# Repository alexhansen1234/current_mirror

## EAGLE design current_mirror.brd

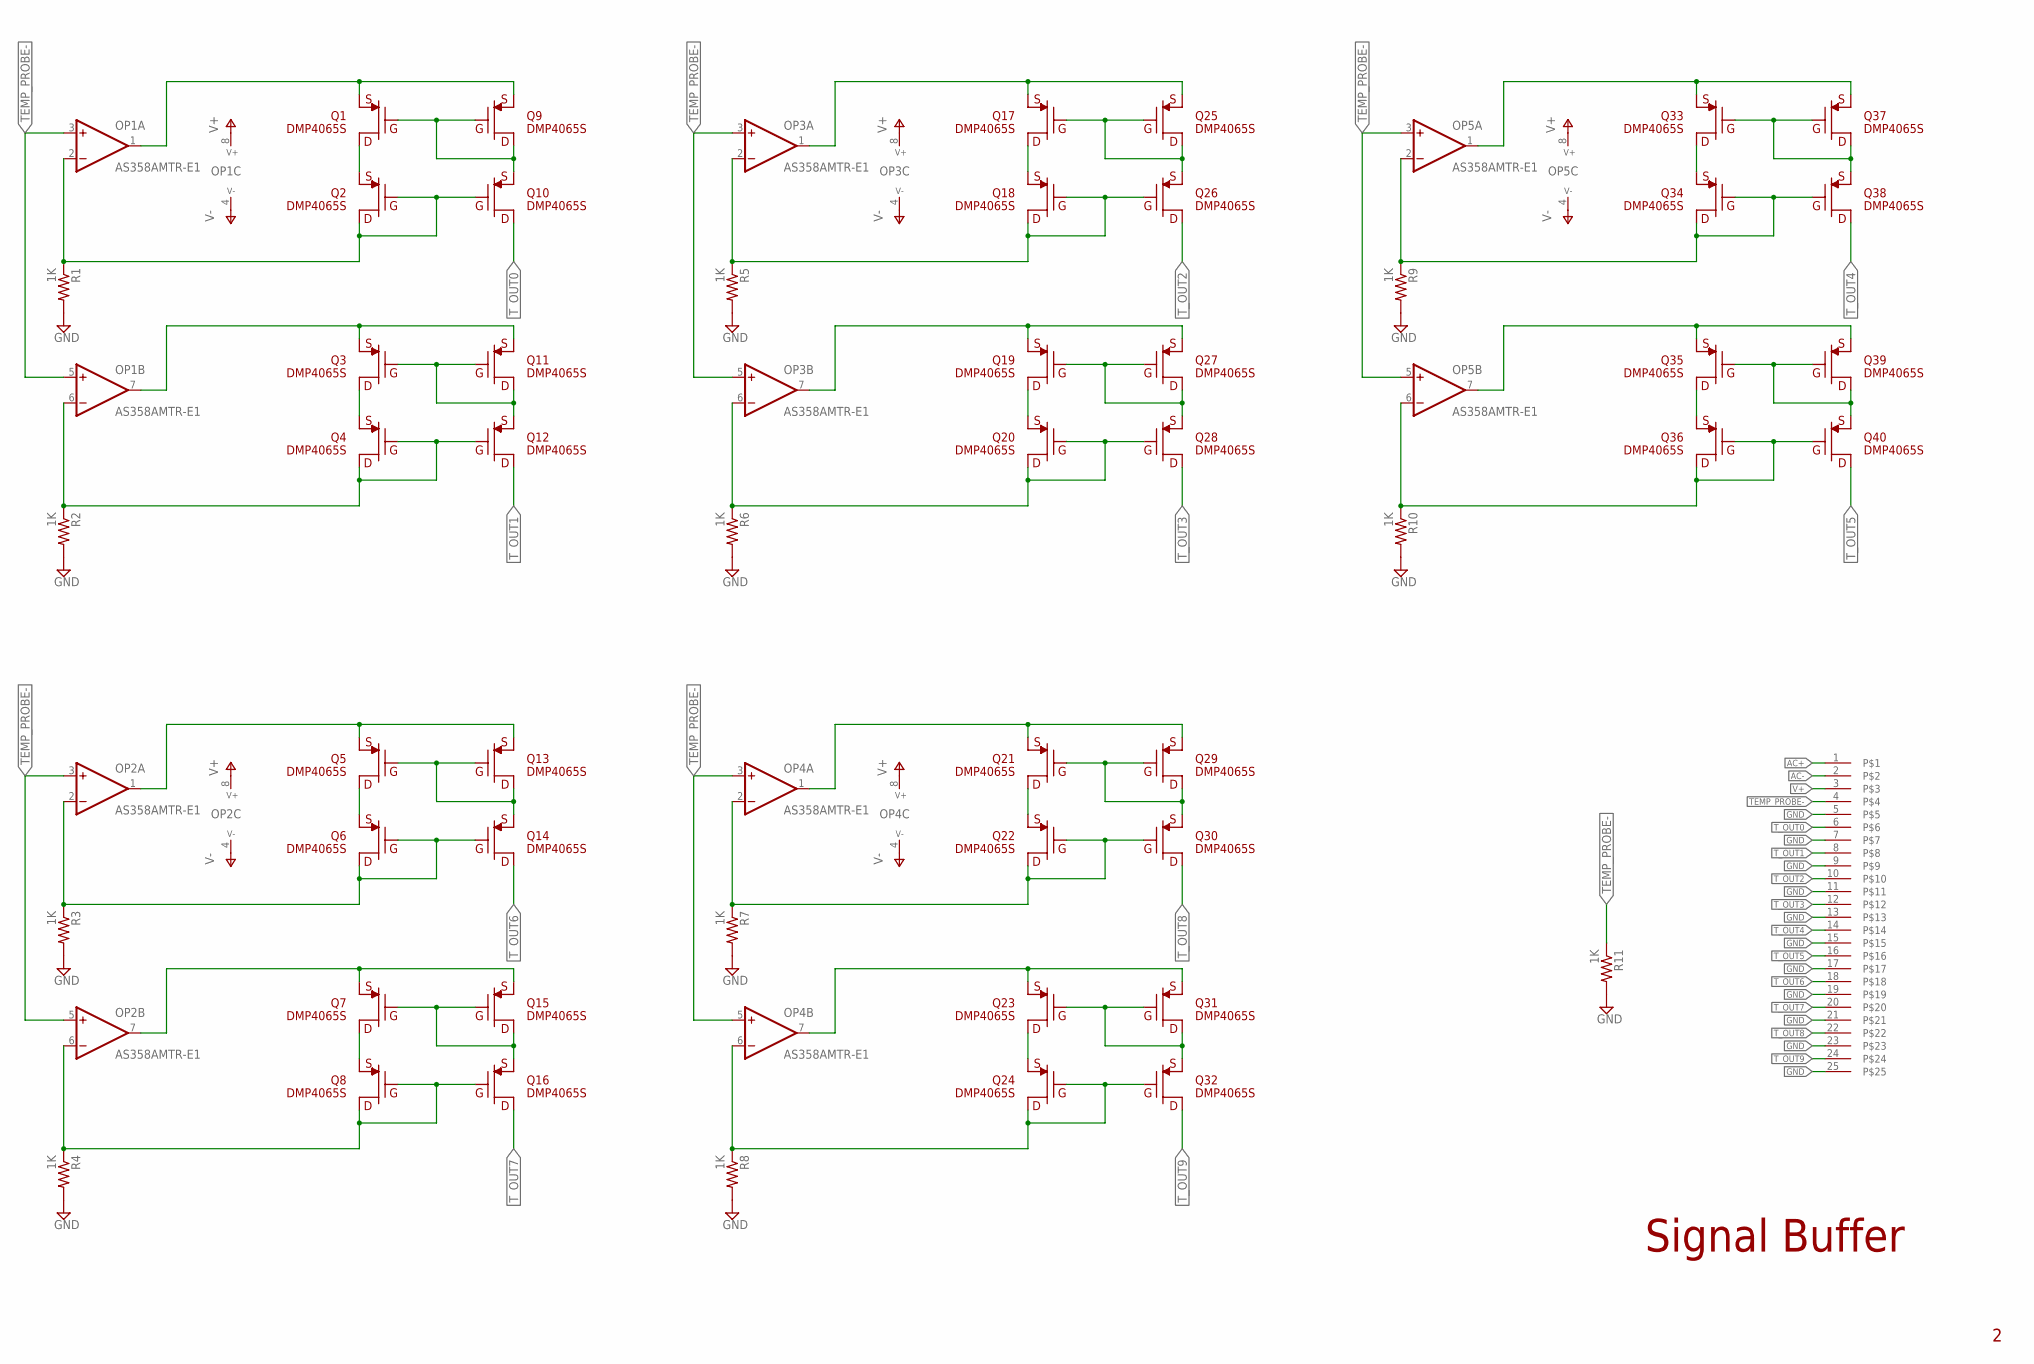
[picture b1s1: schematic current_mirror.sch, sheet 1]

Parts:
J1: 2-282836-6; SCREW_TERMINAL_25
OP1, OP2, OP3, OP4, OP5: AS358AMTR-E1; SOIC-8
Q1, Q2, Q3, Q4, Q5, Q6, Q7, Q8, Q9, Q10, Q11, Q12, Q13, Q14, Q15, Q16, Q17, Q18, Q19, Q20, Q21, Q22, Q23, Q24, Q25, Q26, Q27, Q28, Q29, Q30, Q31, Q32, Q33, Q34, Q35, Q36, Q37, Q38, Q39, Q40: DMP4065S; SOT23
R1, R2, R3, R4, R5, R6, R7, R8, R9, R10, R11: 1K; R1206

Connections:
AC+: J1.1; also elsewhere on the board
AC-: J1.2; also elsewhere on the board
GND: J1.5, J1.7, J1.9, J1.11, J1.13, J1.15, J1.17, J1.19, J1.21, J1.23, J1.25, R1.2, R2.2, R3.2, R4.2, R5.2, R6.2, R7.2, R8.2, R9.2, R10.2, R11.2; also elsewhere on the board
unnamed: OP1.1 (OUT), Q1.2 (S1), Q9.2 (S1)
unnamed: Q1.1 (G1), Q9.1 (G1), Q9.3 (D1), Q10.2 (S1)
unnamed: Q1.3 (D1), Q2.2 (S1)
unnamed: OP1.7 (OUT), Q3.2 (S1), Q11.2 (S1)
unnamed: OP1.2 (-IN), Q2.1 (G1), Q2.3 (D1), Q10.1 (G1), R1.1
unnamed: Q3.1 (G1), Q11.1 (G1), Q11.3 (D1), Q12.2 (S1)
unnamed: Q3.3 (D1), Q4.2 (S1)
unnamed: OP1.6 (-IN), Q4.1 (G1), Q4.3 (D1), Q12.1 (G1), R2.1
unnamed: OP3.1 (OUT), Q17.2 (S1), Q25.2 (S1)
unnamed: Q17.1 (G1), Q25.1 (G1), Q25.3 (D1), Q26.2 (S1)
unnamed: Q17.3 (D1), Q18.2 (S1)
unnamed: OP3.2 (-IN), Q18.1 (G1), Q18.3 (D1), Q26.1 (G1), R5.1
unnamed: OP3.7 (OUT), Q19.2 (S1), Q27.2 (S1)
unnamed: Q19.1 (G1), Q27.1 (G1), Q27.3 (D1), Q28.2 (S1)
unnamed: Q19.3 (D1), Q20.2 (S1)
unnamed: OP3.6 (-IN), Q20.1 (G1), Q20.3 (D1), Q28.1 (G1), R6.1
unnamed: OP5.1 (OUT), Q33.2 (S1), Q37.2 (S1)
unnamed: Q33.1 (G1), Q37.1 (G1), Q37.3 (D1), Q38.2 (S1)
unnamed: Q33.3 (D1), Q34.2 (S1)
unnamed: OP5.2 (-IN), Q34.1 (G1), Q34.3 (D1), Q38.1 (G1), R9.1
unnamed: OP5.7 (OUT), Q35.2 (S1), Q39.2 (S1)
unnamed: Q35.1 (G1), Q39.1 (G1), Q39.3 (D1), Q40.2 (S1)
unnamed: Q35.3 (D1), Q36.2 (S1)
unnamed: OP5.6 (-IN), Q36.1 (G1), Q36.3 (D1), Q40.1 (G1), R10.1
unnamed: OP2.1 (OUT), Q5.2 (S1), Q13.2 (S1)
unnamed: Q5.1 (G1), Q13.1 (G1), Q13.3 (D1), Q14.2 (S1)
unnamed: Q5.3 (D1), Q6.2 (S1)
unnamed: OP2.2 (-IN), Q6.1 (G1), Q6.3 (D1), Q14.1 (G1), R3.1
unnamed: OP2.7 (OUT), Q7.2 (S1), Q15.2 (S1)
unnamed: Q7.1 (G1), Q15.1 (G1), Q15.3 (D1), Q16.2 (S1)
unnamed: Q7.3 (D1), Q8.2 (S1)
unnamed: OP2.6 (-IN), Q8.1 (G1), Q8.3 (D1), Q16.1 (G1), R4.1
unnamed: OP4.1 (OUT), Q21.2 (S1), Q29.2 (S1)
unnamed: Q21.1 (G1), Q29.1 (G1), Q29.3 (D1), Q30.2 (S1)
unnamed: Q21.3 (D1), Q22.2 (S1)
unnamed: OP4.2 (-IN), Q22.1 (G1), Q22.3 (D1), Q30.1 (G1), R7.1
unnamed: OP4.7 (OUT), Q23.2 (S1), Q31.2 (S1)
unnamed: Q23.1 (G1), Q31.1 (G1), Q31.3 (D1), Q32.2 (S1)
unnamed: Q23.3 (D1), Q24.2 (S1)
unnamed: OP4.6 (-IN), Q24.1 (G1), Q24.3 (D1), Q32.1 (G1), R8.1
TEMP_PROBE-: J1.4, OP1.3 (+IN), OP1.5 (+IN), OP2.3 (+IN), OP2.5 (+IN), OP3.3 (+IN), OP3.5 (+IN), OP4.3 (+IN), OP4.5 (+IN), OP5.3 (+IN), OP5.5 (+IN), R11.1
T_OUT0: J1.6, Q10.3 (D1)
T_OUT1: J1.8, Q12.3 (D1)
T_OUT2: J1.10, Q26.3 (D1)
T_OUT3: J1.12, Q28.3 (D1)
T_OUT4: J1.14, Q38.3 (D1)
T_OUT5: J1.16, Q40.3 (D1)
T_OUT6: J1.18, Q14.3 (D1)
T_OUT7: J1.20, Q16.3 (D1)
T_OUT8: J1.22, Q30.3 (D1)
T_OUT9: J1.24, Q32.3 (D1)
V+: J1.3, OP1.8 (V+), OP2.8 (V+), OP3.8 (V+), OP4.8 (V+), OP5.8 (V+); also elsewhere on the board
V-: OP1.4 (V-), OP2.4 (V-), OP3.4 (V-), OP4.4 (V-), OP5.4 (V-); also elsewhere on the board

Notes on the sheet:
Signal Buffer

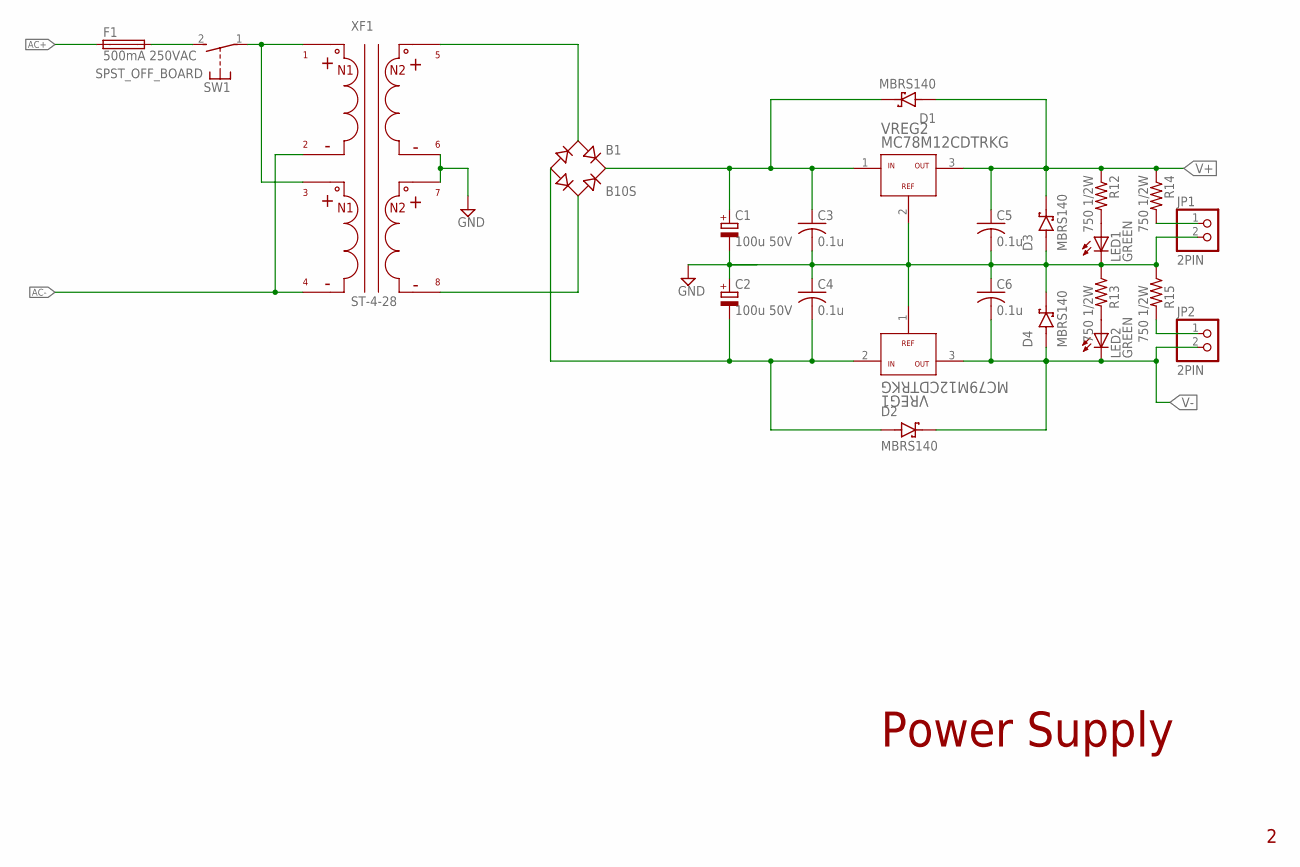
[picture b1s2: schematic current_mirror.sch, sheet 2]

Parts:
B1: B10S; MBS
C1, C2: 100u 50V; 153CLV-1010
C3, C4, C5, C6: 0.1u; C0603
D1, D2, D3, D4: MBRS140; DIO_MBRS140
F1: 500mA 250VAC; SH22
JP1, JP2: 2PIN; 1X02
LED1, LED2: GREEN; CHIP-LED0603
R12, R13, R14, R15: 750 1/2W; R1206
SW1: SPST_OFF_BOARD
VREG1: MC79M12CDTRKG; DPAK-3
VREG2: MC78M12CDTRKG; DPAK-3
XF1: ST-4-28

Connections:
AC+: F1.1; also elsewhere on the board
AC-: XF1.P$2, XF1.P$4; also elsewhere on the board
GND: C1.-, C2.+, C3.2, C4.1, C5.2, C6.1, D3.A, D4.C (K), JP1.2, LED1.C, R13.1, R15.1, VREG1.1 (GND), VREG2.2 (GND), XF1.P$6, XF1.P$7; also elsewhere on the board
unnamed: B1.AC1, XF1.P$5
unnamed: B1.AC2, XF1.P$8
unnamed: SW1.1, XF1.P$1, XF1.P$3
unnamed: F1.2, SW1.2 (S)
unnamed: LED1.A, R12.2
unnamed: LED2.A, R13.2
unnamed: JP2.1, R15.2
unnamed: JP1.1, R14.2
R+: B1.+, C1.+, C3.1, D1.C (K), VREG2.1 (VIN)
R-: B1.-, C2.-, C4.2, D2.A, VREG1.2 (VIN)
V+: C5.1, D1.A, D3.C (K), R12.1, R14.1, VREG2.3 (VOUT); also elsewhere on the board
V-: C6.2, D2.C (K), D4.A, JP2.2, LED2.C, VREG1.3 (VOUT); also elsewhere on the board

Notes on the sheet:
Power Supply

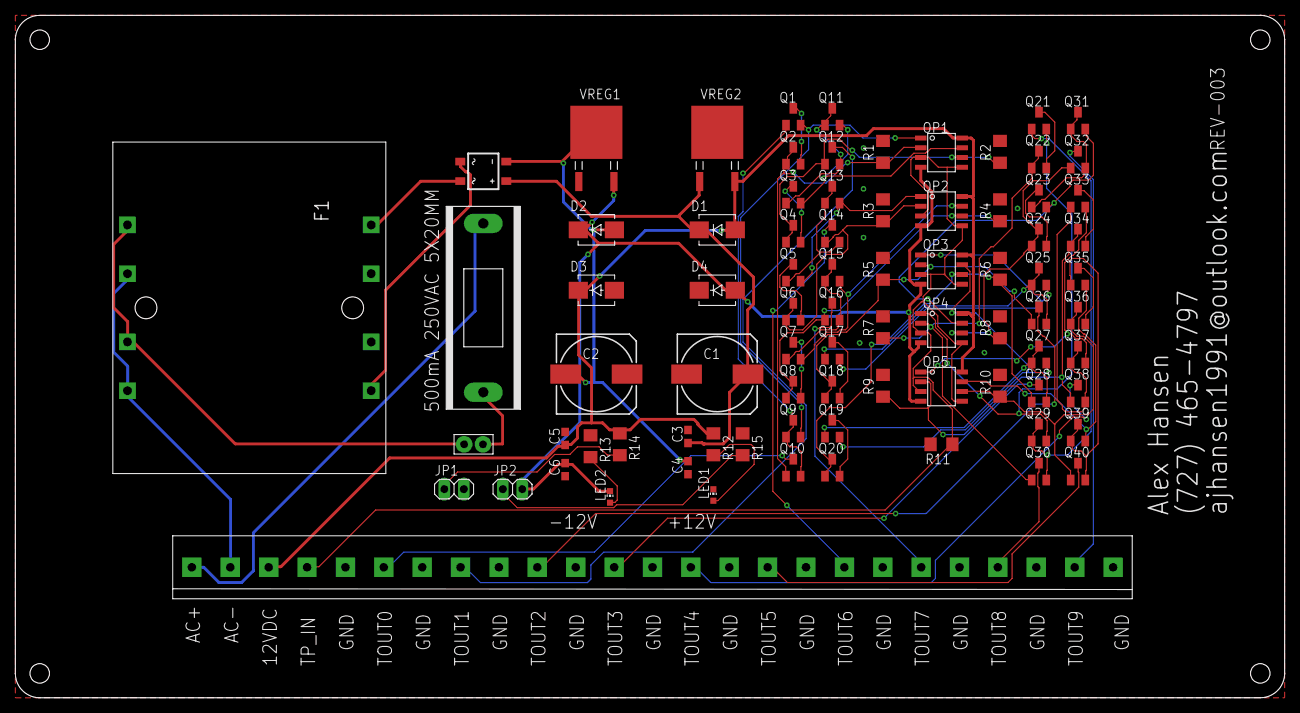
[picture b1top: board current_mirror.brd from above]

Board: 2 copper layers, 165.4 x 88.9 mm, 81 parts (0 on the bottom side), 66 nets.

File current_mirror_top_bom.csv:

Comment, Designator, Footprint, LCSC Part #(optional)
B10S, B1, MBS, C2487
100u 50V, C1, 153CLV-1010, C134808
100u 50V, C2, 153CLV-1010, C134808
0.1u, C3, C0603, C14663
0.1u, C4, C0603, C14663
0.1u, C5, C0603, C14663
0.1u, C6, C0603, C14663
MBRS140, D1, DIO_MBRS140, C133091
MBRS140, D2, DIO_MBRS140, C133091
MBRS140, D3, DIO_MBRS140, C133091
MBRS140, D4, DIO_MBRS140, C133091
GREEN, LED1, CHIP-LED0603, C72043
GREEN, LED2, CHIP-LED0603, C72043
AS358AMTR-E1, OP1, SOIC-8, C141322
AS358AMTR-E1, OP2, SOIC-8, C141322
AS358AMTR-E1, OP3, SOIC-8, C141322
AS358AMTR-E1, OP4, SOIC-8, C141322
AS358AMTR-E1, OP5, SOIC-8, C141322
DMP4065S, Q1, SOT23, C182476
DMP4065S, Q2, SOT23, C182476
DMP4065S, Q3, SOT23, C182476
DMP4065S, Q4, SOT23, C182476
DMP4065S, Q5, SOT23, C182476
DMP4065S, Q6, SOT23, C182476
DMP4065S, Q7, SOT23, C182476
DMP4065S, Q8, SOT23, C182476
DMP4065S, Q9, SOT23, C182476
DMP4065S, Q10, SOT23, C182476
DMP4065S, Q11, SOT23, C182476
DMP4065S, Q12, SOT23, C182476
DMP4065S, Q13, SOT23, C182476
DMP4065S, Q14, SOT23, C182476
DMP4065S, Q15, SOT23, C182476
DMP4065S, Q16, SOT23, C182476
DMP4065S, Q17, SOT23, C182476
DMP4065S, Q18, SOT23, C182476
DMP4065S, Q19, SOT23, C182476
DMP4065S, Q20, SOT23, C182476
DMP4065S, Q21, SOT23, C182476
DMP4065S, Q22, SOT23, C182476
DMP4065S, Q23, SOT23, C182476
DMP4065S, Q24, SOT23, C182476
DMP4065S, Q25, SOT23, C182476
DMP4065S, Q26, SOT23, C182476
DMP4065S, Q27, SOT23, C182476
DMP4065S, Q28, SOT23, C182476
DMP4065S, Q29, SOT23, C182476
DMP4065S, Q30, SOT23, C182476
DMP4065S, Q31, SOT23, C182476
DMP4065S, Q32, SOT23, C182476
DMP4065S, Q33, SOT23, C182476
DMP4065S, Q34, SOT23, C182476
DMP4065S, Q35, SOT23, C182476
DMP4065S, Q36, SOT23, C182476
DMP4065S, Q37, SOT23, C182476
DMP4065S, Q38, SOT23, C182476
DMP4065S, Q39, SOT23, C182476
DMP4065S, Q40, SOT23, C182476
1K, R1, R1206, C95218
1K, R2, R1206, C95218
1K, R3, R1206, C95218
1K, R4, R1206, C95218
1K, R5, R1206, C95218
1K, R6, R1206, C95218
1K, R7, R1206, C95218
1K, R8, R1206, C95218
1K, R9, R1206, C95218
1K, R10, R1206, C95218
1K, R11, R1206, C95218
750 1/2W, R12, R1206,  C4410
750 1/2W, R13, R1206,  C4410
750 1/2W, R14, R1206,  C4410
750 1/2W, R15, R1206,  C4410
MC79M12CDTRKG, VREG1, DPAK-3, C67852
MC78M12CDTRKG, VREG2, DPAK-3, C67851

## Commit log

2020-11-07 init
2020-11-07 update gitignore

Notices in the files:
parts and their libraries:
COPYRIGHT: Copyright (C) 2016 Accelerated Designs. All rights reserved
